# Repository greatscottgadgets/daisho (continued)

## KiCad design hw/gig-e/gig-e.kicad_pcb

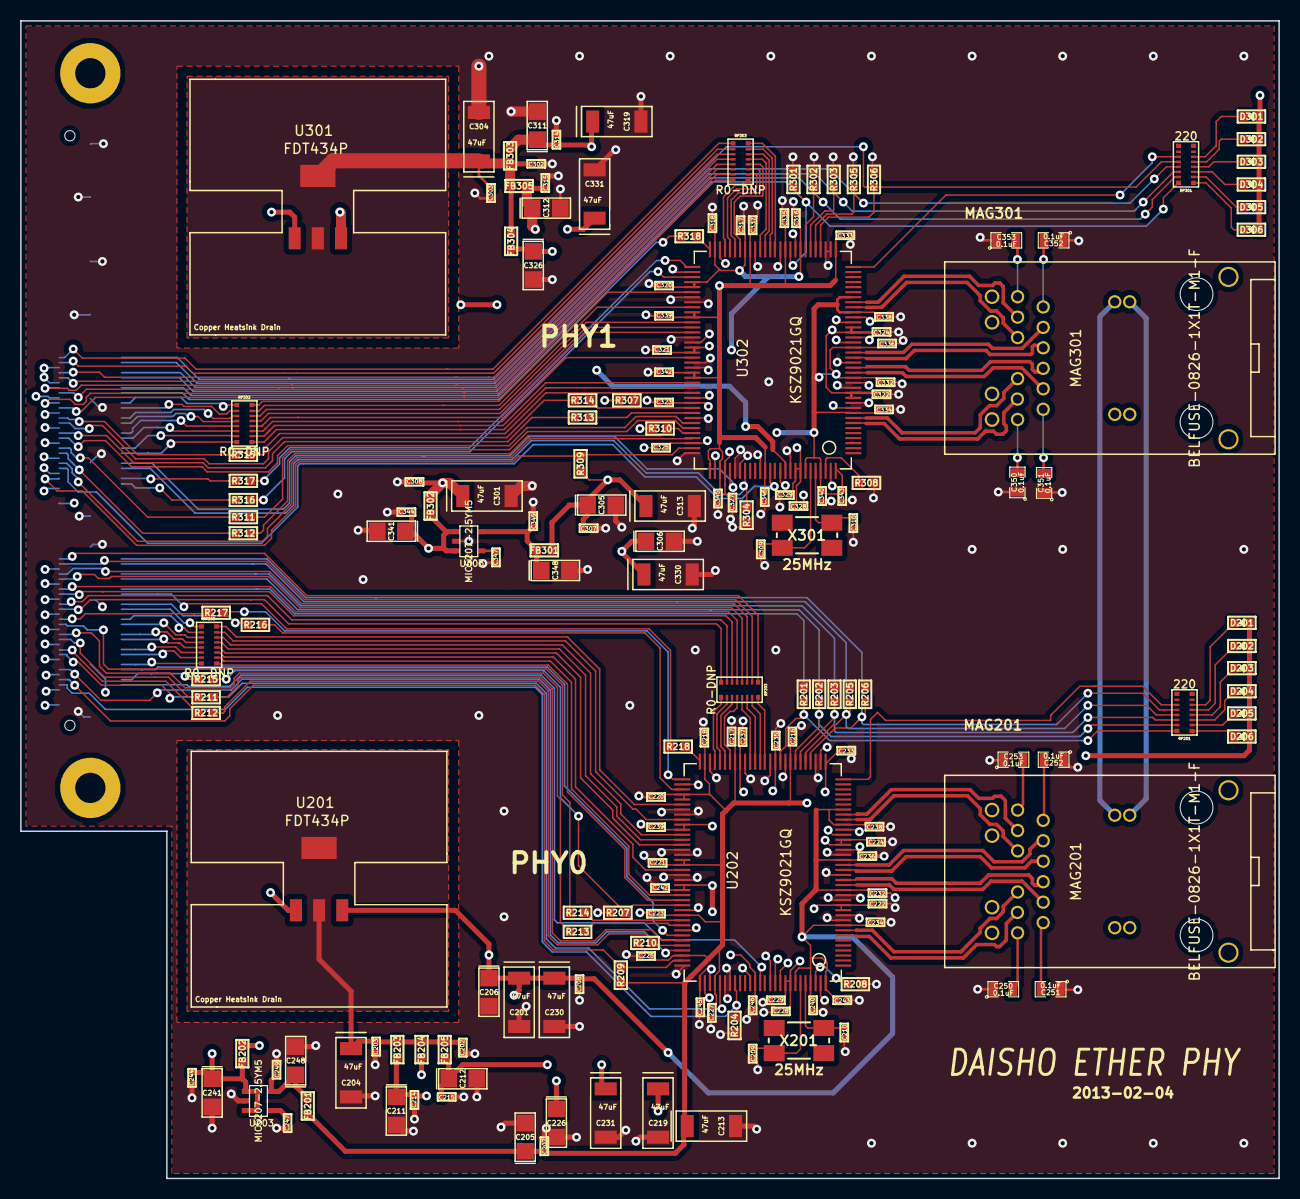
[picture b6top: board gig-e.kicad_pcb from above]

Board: 4 copper layers, 125.0 x 115.0 mm, 181 parts (1 on the bottom side), 185 nets.

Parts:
C201, C204, C213, C219, C230, C231, C301, C304, C313, C319, C330, C331: 47uF; gsg-2312
C202, C207, C208, C214, C215, C228, C244, C249, C302, C307, C308, C314, C315, C328, C344, C349: 0.1uF; GSG-0402
C203, C216, C217, C218, C220, C221, C222, C223, C224, C225, C227, C229, C232, C233, C234, C235, C236, C237, C238, C239, C240, C242, C243, C245, C246, C303, C316, C317, C318, C320, C321, C322, C323, C324, C325, C327, C329, C332, C333, C334, C335, C336, C337, C338, C339, C340, C342, C343, C345, C346: 10nF; GSG-0402
C205, C206, C211, C212, C226, C241, C248, C305, C306, C311, C312, C326, C341, C348: 10uF; gsg-sm1206p
C209, C210, C309, C310: 22pF; GSG-0402
C247, C347: 470pF; GSG-0402
C250, C251, C252, C253, C350, C351, C352, C353: 0.1uF; SM0805
D201: PHY0_LINK10-YLW; GSG-0603D
D202: PHY0_LINK100-GRN; GSG-0603D
D203: PHY0_LINK1000-BLUE; GSG-0603D
D204: PHY0_DUPLEX-YLW; GSG-0603D
D205: PHY0_RX-GRN; GSG-0603D
D206: PHY0_TX-GRN; GSG-0603D
D301: PHY1_LINK10-YLW; GSG-0603D
D302: PHY1_LINK100-GRN; GSG-0603D
D303: PHY1_LINK1000-BLUE; GSG-0603D
D304: PHY1_DUPLEX-YLW; GSG-0603D
D305: PHY1_RX-GRN; GSG-0603D
D306: PHY1_TX-GRN; GSG-0603D
FB201, FB202, FB203, FB204, FB205, FB301, FB302, FB303, FB304, FB305: FBEAD; GSG-0603
JP101: TERASIC-HSMC; TERASIC-HSMC-WITH-MOUNTS
MAG201, MAG301: BELFUSE-0826-1X1T-M1-F; BELFUSE-MAG
R201, R202, R203, R205, R206, R207, R301, R302, R303, R305, R306, R307: 1k; GSG-0603
R204, R304: 4.7k; GSG-0603
R208, R308: 4.99K 1%; GSG-0603
R209, R210, R309, R310: 4.7K; GSG-0603
R211, R212, R213, R214, R215, R216, R217, R218, R311, R312, R313, R314, R315, R316, R317, R318: 0.0-NP; GSG-0603
RP201, RP301: 220; 1506-RPACK
RP202, RP203, RP302, RP303: R0-DNP; 1506-RPACK
U201, U301: FDT434P; FDT434P-SOT223
U202, U302: KSZ9021GQ; GSG-PQFP128
U203, U303: MIC5207-2.5YM5; SOT23-5
X201, X301: 25MHz; ABMM2

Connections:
+2.5V: C248.1, C249.1, C348.1, C349.1, FB201.1, FB301.1, U203.5, U303.5
+3.3V: C241.1, C244.1, C341.1, C344.1, FB202.1, FB302.1, JP101.45, JP101.51, JP101.57, JP101.63, JP101.69, JP101.75, JP101.81, JP101.87, JP101.93, JP101.99, JP101.105, JP101.111, JP101.117, JP101.123, JP101.129, JP101.135, JP101.141, JP101.147, JP101.153, JP101.159, U203.1, U203.3, U303.1, U303.3
/GigE Phy0/AVDDH: C201.1, C206.1, C208.1, C230.1, C232.1, C234.1, C236.1, C238.1, C240.1, C243.1, FB202.2, U201.S, U202.9, U202.16, U202.22, U202.29, U202.32, U202.122, U202.125, U202.128
/GigE Phy0/AVDDL: C211.1, C214.1, C219.1, C222.1, C224.1, FB203.2, U202.12, U202.13, U202.25, U202.26
/GigE Phy0/AVDDL_PMOS: C202.1, C203.1, C204.1, FB203.1, FB204.1, FB205.1, U201.D
/GigE Phy0/AVDD_PLL: C226.1, C228.1, C229.1, FB204.2, U202.120, U202.121
/GigE Phy0/DVDDH: C205.1, C207.1, C213.1, C216.1, C217.1, C218.1, C220.1, C221.1, C223.1, C225.1, C227.1, D201.1, D202.1, D203.1, D204.1, D205.1, D206.1, FB201.2, R209.1, R210.1, U202.46, U202.57, U202.63, U202.68, U202.69, U202.81, U202.82, U202.92, U202.100, U202.106
/GigE Phy0/DVDDL: C212.1, C215.1, C231.1, C233.1, C235.1, C237.1, C239.1, C242.1, C245.1, C246.1, FB205.2, U202.39, U202.49, U202.56, U202.74, U202.75, U202.86, U202.87, U202.103, U202.105, U202.114
/GigE Phy0/GTX_CLK: R217.1, U202.65
/GigE Phy0/LDO_O: U201.G, U202.118
/GigE Phy0/LED1_D: D206.2, RP201.9
/GigE Phy0/LED2_D: D205.2, RP201.10
/GigE Phy0/LED3_D: D204.2, RP201.11
/GigE Phy0/LED4_D: D203.2, RP201.12
/GigE Phy0/LED5_D: D202.2, RP201.13
/GigE Phy0/LED6: RP201.3, U202.38
/GigE Phy0/LED6_D: D201.2, RP201.14
/GigE Phy0/RXD0: RP202.1, U202.89
/GigE Phy0/RXD1: RP202.2, U202.88
/GigE Phy0/RXD2: RP202.3, U202.83
/GigE Phy0/RXD3: RP202.4, U202.78
/GigE Phy0/RXD4: RP202.5, U202.77
/GigE Phy0/RXD5: RP202.6, U202.76
/GigE Phy0/RXD6: RP202.7, U202.73
/GigE Phy0/RXD7: RP202.8, U202.70
/GigE Phy0/TXD0: RP203.8, U202.51
/GigE Phy0/TXD1: RP203.7, U202.52
/GigE Phy0/TXD2: RP203.6, U202.53
/GigE Phy0/TXD3: RP203.5, U202.54
/GigE Phy0/TXD4: RP203.4, U202.58
/GigE Phy0/TXD5: RP203.3, U202.59
/GigE Phy0/TXD6: RP203.2, U202.60
/GigE Phy0/TXD7: RP203.1, U202.61
/GigE Phy1/AVDDH: C301.1, C306.1, C308.1, C330.1, C332.1, C334.1, C336.1, C338.1, C340.1, C343.1, FB302.2, U301.S, U302.9, U302.16, U302.22, U302.29, U302.32, U302.122, U302.125, U302.128
/GigE Phy1/AVDDL: C311.1, C314.1, C319.1, C322.1, C324.1, FB303.2, U302.12, U302.13, U302.25, U302.26
/GigE Phy1/AVDD_PLL: C326.1, C328.1, C329.1, FB304.2, U302.120, U302.121
/GigE Phy1/DVDDH: C305.1, C307.1, C313.1, C316.1, C317.1, C318.1, C320.1, C321.1, C323.1, C325.1, C327.1, D301.1, D302.1, D303.1, D304.1, D305.1, D306.1, FB301.2, R309.1, R310.1, U302.46, U302.57, U302.63, U302.68, U302.69, U302.81, U302.82, U302.92, U302.100, U302.106
/GigE Phy1/DVDDL: C312.1, C315.1, C331.1, C333.1, C335.1, C337.1, C339.1, C342.1, C345.1, C346.1, FB305.2, U302.39, U302.49, U302.56, U302.74, U302.75, U302.86, U302.87, U302.103, U302.105, U302.114
/GigE Phy1/GTX_CLK: R317.1, U302.65
/GigE Phy1/LDO_O: U301.G, U302.118
/GigE Phy1/LED1_D: D306.2, RP301.9
/GigE Phy1/LED2_D: D305.2, RP301.10
/GigE Phy1/LED3_D: D304.2, RP301.11
/GigE Phy1/LED4_D: D303.2, RP301.12
/GigE Phy1/LED5_D: D302.2, RP301.13
/GigE Phy1/LED6: RP301.3, U302.38
/GigE Phy1/LED6_D: D301.2, RP301.14
/GigE Phy1/PHY1_AVDDL_PMOS: C302.1, C303.1, C304.1, FB303.1, FB304.1, FB305.1, U301.D
/GigE Phy1/RXD0: RP302.1, U302.89
/GigE Phy1/RXD1: RP302.2, U302.88
/GigE Phy1/RXD2: RP302.3, U302.83
/GigE Phy1/RXD3: RP302.4, U302.78
/GigE Phy1/RXD4: RP302.5, U302.77
/GigE Phy1/RXD5: RP302.6, U302.76
/GigE Phy1/RXD6: RP302.7, U302.73
/GigE Phy1/RXD7: RP302.8, U302.70
/GigE Phy1/TXD0: RP303.8, U302.51
/GigE Phy1/TXD1: RP303.7, U302.52
/GigE Phy1/TXD2: RP303.6, U302.53
/GigE Phy1/TXD3: RP303.5, U302.54
/GigE Phy1/TXD4: RP303.4, U302.58
/GigE Phy1/TXD5: RP303.3, U302.59
/GigE Phy1/TXD6: RP303.2, U302.60
/GigE Phy1/TXD7: RP303.1, U302.61
GND: C201.2, C202.2, C203.2, C204.2, C205.2, C206.2, C207.2, C208.2, C209.1, C210.1, C211.2, C212.2, C213.2, C214.2, C215.2, C216.2, C217.2, C218.2, C219.2, C220.2, C221.2, C222.2, C223.2, C224.2, C225.2, C226.2, C227.2, C228.2, C229.2, C230.2, C231.2, C232.2, C233.2, C234.2, C235.2, C236.2, C237.2, C238.2, C239.2, C240.2, C241.2, C242.2, C243.2, C244.2, C245.2, C246.2, C247.2, C248.2, C249.2, C250.1, C251.1, C252.1, C253.1, C301.2, C302.2, C303.2, C304.2, C305.2, C306.2, C307.2, C308.2, C309.1, C310.1, C311.2, C312.2, C313.2, C314.2, C315.2, C316.2, C317.2, C318.2, C319.2, C320.2, C321.2, C322.2, C323.2, C324.2, C325.2, C326.2, C327.2, C328.2, C329.2, C330.2, C331.2, C332.2, C333.2, C334.2, C335.2, C336.2, C337.2, C338.2, C339.2, C340.2, C341.2, C342.2, C343.2, C344.2, C345.2, C346.2, C347.2, C348.2, C349.2, C350.1, C351.1, C352.1, C353.1, JP101.161, JP101.162, JP101.163, JP101.164, JP101.165, JP101.166, JP101.167, JP101.168, JP101.169, JP101.170, JP101.171, JP101.172, R201.2, R202.2, R203.2, R204.2, R205.2, R206.2, R207.2, R208.1, R301.2, R302.2, R303.2, R304.2, R305.2, R306.2, R307.2, R308.1, U202.10, U202.11, U202.14, U202.15, U202.19, U202.23, U202.24, U202.27, U202.28, U202.40, U202.41, U202.47, U202.50, U202.55, U202.62, U202.66, U202.71, U202.72, U202.79, U202.80, U202.84, U202.85, U202.91, U202.95, U202.102, U202.104, U202.108, U202.109, U202.113, U202.117, U202.119, U202.127, U203.2, U302.10, U302.11, U302.14, U302.15, U302.19, U302.23, U302.24, U302.27, U302.28, U302.40, U302.41, U302.47, U302.50, U302.55, U302.62, U302.66, U302.71, U302.72, U302.79, U302.80, U302.84, U302.85, U302.91, U302.95, U302.102, U302.104, U302.108, U302.109, U302.113, U302.117, U302.119, U302.127, U303.2
MAG_VC_1: MAG201.13, MAG301.13
MAG_VC_2: MAG201.14, MAG301.14
MAG_VC_3: MAG201.15, MAG301.15
MAG_VC_4: MAG201.16, MAG301.16
unnamed: R208.2, U202.126
unnamed: C253.2, MAG201.7
unnamed: C251.2, MAG201.6
unnamed: C252.2, MAG201.1
unnamed: C250.2, MAG201.12
unnamed: C247.1, U203.4
unnamed: C209.2, U202.123, X201.2
unnamed: C210.2, U202.124, X201.1
unnamed: R308.2, U302.126
unnamed: C353.2, MAG301.7
unnamed: C351.2, MAG301.6
unnamed: C352.2, MAG301.1
unnamed: C350.2, MAG301.12
unnamed: C347.1, U303.4
unnamed: C309.2, U302.123, X301.2
unnamed: C310.2, U302.124, X301.1
PHY0_CLK125_NDO: JP101.139, U202.107
PHY0_COL: JP101.145, U202.99
PHY0_CRS: JP101.146, U202.96
PHY0_GM_GTK_CLK: JP101.125, R217.2
PHY0_GM_MDC: JP101.133, R211.2
PHY0_GM_MIO: JP101.137, R212.2
PHY0_GM_RXD0: JP101.144, RP202.16
PHY0_GM_RXD1: JP101.140, RP202.15
PHY0_GM_RXD2: JP101.138, RP202.14
PHY0_GM_RXD3: JP101.134, RP202.13
PHY0_GM_RXD4: JP101.132, RP202.12
PHY0_GM_RXD5: JP101.128, RP202.11
PHY0_GM_RXD6: JP101.126, RP202.10
PHY0_GM_RXD7: JP101.122, RP202.9
PHY0_GM_RXDV: JP101.150, R215.2
PHY0_GM_RX_CLK: JP101.131, R213.2
PHY0_GM_RX_ERR: JP101.127, R214.2
PHY0_GM_TXD0: JP101.101, RP203.9
PHY0_GM_TXD1: JP101.103, RP203.10
PHY0_GM_TXD2: JP101.107, RP203.11
PHY0_GM_TXD3: JP101.109, RP203.12
PHY0_GM_TXD4: JP101.113, RP203.13
PHY0_GM_TXD5: JP101.115, RP203.14
PHY0_GM_TXD6: JP101.119, RP203.15
PHY0_GM_TXD7: JP101.121, RP203.16
PHY0_GM_TX_EN: JP101.120, R216.2
PHY0_GM_TX_ER: JP101.116, R218.2
PHY0_HW_RST: JP101.151, R204.1, U202.110
PHY0_INT_N: JP101.149, R209.2, U202.101
PHY0_MDC: R211.1, U202.97
PHY0_MDIO: R210.2, R212.1, U202.98
PHY0_PHYADDR0: JP101.114, R201.1, RP201.8, U202.48
PHY0_PHYADDR1: JP101.110, R202.1, RP201.7, U202.45
PHY0_PHYADDR2: JP101.108, R203.1, RP201.6, U202.44
PHY0_PHYADDR3: JP101.104, R205.1, RP201.5, U202.43
PHY0_PHYADDR4: JP101.102, R206.1, RP201.4, U202.42
PHY0_RXDV: R207.1, R215.1, U202.90
PHY0_RX_CLK: R213.1, U202.94
PHY0_RX_ERR: R214.1, U202.93
PHY0_TXRXM_A: MAG201.10, U202.8
PHY0_TXRXM_B: MAG201.4, U202.18
PHY0_TXRXM_C: MAG201.2, U202.21
PHY0_TXRXM_D: MAG201.8, U202.31
PHY0_TXRXP_A: MAG201.11, U202.7
PHY0_TXRXP_B: MAG201.5, U202.17
PHY0_TXRXP_C: MAG201.3, U202.20
PHY0_TXRXP_D: MAG201.9, U202.30
PHY0_TX_CLK: JP101.152, U202.115
PHY0_TX_EN: R216.1, U202.67
PHY0_TX_ER: R218.1, U202.64
PHY1_CLK125_NDO: JP101.84, U302.107
PHY1_COL: JP101.83, U302.99
PHY1_CRS: JP101.73, U302.96
PHY1_GM_GTK_CLK: JP101.90, R317.2
PHY1_GM_MDC: JP101.77, R311.2
PHY1_GM_MIO: JP101.79, R312.2
PHY1_GM_RXD0: JP101.80, RP302.16
PHY1_GM_RXD1: JP101.78, RP302.15
PHY1_GM_RXD2: JP101.74, RP302.14
PHY1_GM_RXD3: JP101.72, RP302.13
PHY1_GM_RXD4: JP101.68, RP302.12
PHY1_GM_RXD5: JP101.66, RP302.11
PHY1_GM_RXD6: JP101.62, RP302.10
PHY1_GM_RXD7: JP101.60, RP302.9
PHY1_GM_RXDV: JP101.65, R315.2
PHY1_GM_RX_CLK: JP101.71, R313.2
PHY1_GM_RX_ERR: JP101.67, R314.2
PHY1_GM_TXD0: JP101.41, RP303.9
PHY1_GM_TXD1: JP101.43, RP303.10
PHY1_GM_TXD2: JP101.47, RP303.11
PHY1_GM_TXD3: JP101.49, RP303.12
PHY1_GM_TXD4: JP101.53, RP303.13
PHY1_GM_TXD5: JP101.55, RP303.14
PHY1_GM_TXD6: JP101.59, RP303.15
PHY1_GM_TXD7: JP101.61, RP303.16
PHY1_GM_TX_EN: JP101.92, R316.2
PHY1_GM_TX_ER: JP101.56, R318.2
PHY1_HW_RST: JP101.86, R304.1, U302.110
PHY1_INT_N: JP101.89, R309.2, U302.101
PHY1_MDC: R311.1, U302.97
PHY1_MDIO: R310.2, R312.1, U302.98
PHY1_PHYADDR0: JP101.54, R301.1, RP301.8, U302.48
PHY1_PHYADDR1: JP101.50, R302.1, RP301.7, U302.45
PHY1_PHYADDR2: JP101.48, R303.1, RP301.6, U302.44
PHY1_PHYADDR3: JP101.44, R305.1, RP301.5, U302.43
PHY1_PHYADDR4: JP101.42, R306.1, RP301.4, U302.42
PHY1_RXDV: R307.1, R315.1, U302.90
PHY1_RX_CLK: R313.1, U302.94
PHY1_RX_ERR: R314.1, U302.93
PHY1_TXRXM_A: MAG301.10, U302.8
PHY1_TXRXM_B: MAG301.4, U302.18
PHY1_TXRXM_C: MAG301.2, U302.21
PHY1_TXRXM_D: MAG301.8, U302.31
PHY1_TXRXP_A: MAG301.11, U302.7
PHY1_TXRXP_B: MAG301.5, U302.17
PHY1_TXRXP_C: MAG301.3, U302.20
PHY1_TXRXP_D: MAG301.9, U302.30
PHY1_TX_CLK: JP101.85, U302.115
PHY1_TX_EN: R316.1, U302.67
PHY1_TX_ER: R318.1, U302.64

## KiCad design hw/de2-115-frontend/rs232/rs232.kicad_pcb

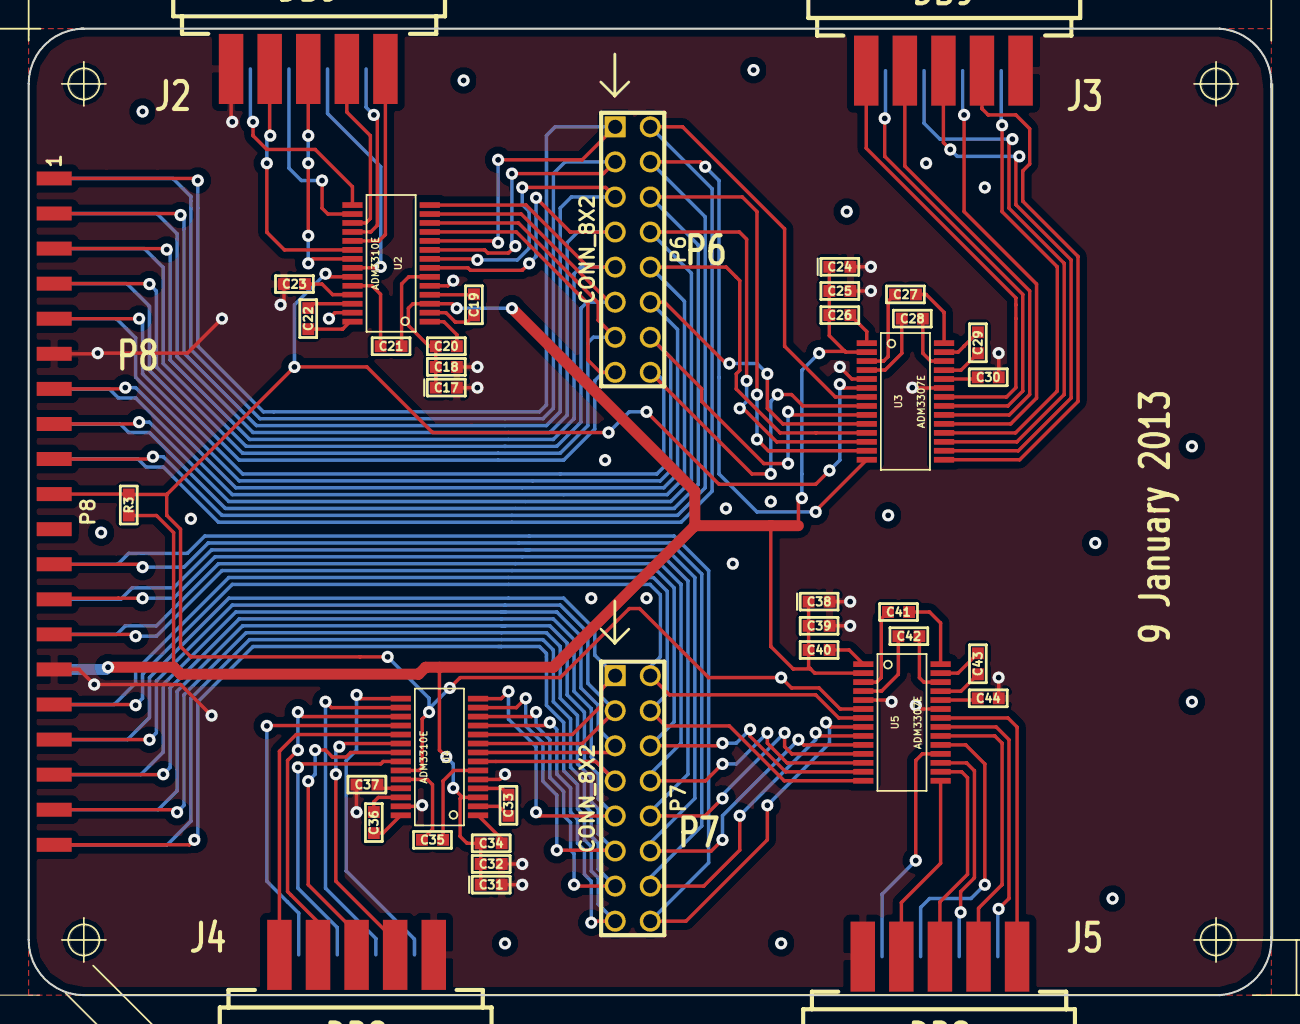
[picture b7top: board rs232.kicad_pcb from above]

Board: 2 copper layers, 90.0 x 70.0 mm, 41 parts (0 on the bottom side), 99 nets.

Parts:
70mm: 90mm; dp_devices-PCB7X9
C17, C24, C31, C38: T10uF; GSG-0603P
C18, C19, C20, C21, C22, C23, C25, C26, C27, C28, C29, C30, C32, C33, C34, C35, C36, C37, C39, C40, C41, C42, C43, C44: 0.1uF; GSG-0603
J2, J4: DB9; DB9M_CI
J3, J5: DB9; DB9F_CI
P6, P7: CONN_8X2; pin_array_8x2
P8: CONN_20X2; GSG-HEADER-2x20-EDGE
R3: 10K; GSG-0603
U2, U4: ADM3310E; tssop-28
U3, U5: ADM3307E; tssop-28

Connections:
+3.3V: C17.1, C18.1, C20.2, C24.1, C25.1, C26.1, C31.1, C32.1, C34.2, C38.1, C39.1, C40.1, P8.29, R3.2, U2.3, U3.2, U4.3, U5.2
/Pair A-B/CD-A-232: J2.1, U2.19
/Pair A-B/CD-B-232: J3.1, U3.22
/Pair A-B/CTS-A-232: J2.8, U2.16
/Pair A-B/CTS-B-232: J3.8, U3.19
/Pair A-B/DSR-A-232: J2.6, U2.18
/Pair A-B/DSR-B-232: J3.6, U3.21
/Pair A-B/DTR-A-232: J2.4, U2.20
/Pair A-B/DTR-B-232: J3.4, U3.15
/Pair A-B/RI-A-232: J2.9, U2.15
/Pair A-B/RI-B-232: J3.9, U3.18
/Pair A-B/RTS-A-232: J2.7, U2.22
/Pair A-B/RTS-B-232: J3.7, U3.17
/Pair A-B/RXD-A-232: J2.2, U2.17
/Pair A-B/RXD-B-232: J3.2, U3.20
/Pair A-B/TXD-A-232: J2.3, U2.21
/Pair A-B/TXD-B-232: J3.3, U3.16
/Pair C-D/CD-C-232: J4.1, U4.19
/Pair C-D/CD-D-232: J5.1, U5.22
/Pair C-D/CTS-C-232: J4.8, U4.16
/Pair C-D/CTS-D-232: J5.8, U5.19
/Pair C-D/DSR-C-232: J4.6, U4.18
/Pair C-D/DSR-D-232: J5.6, U5.21
/Pair C-D/DTR-C-232: J4.4, U4.20
/Pair C-D/DTR-D-232: J5.4, U5.15
/Pair C-D/RI-C-232: J4.9, U4.15
/Pair C-D/RI-D-232: J5.9, U5.18
/Pair C-D/RTS-C-232: J4.7, U4.22
/Pair C-D/RTS-D-232: J5.7, U5.17
/Pair C-D/RXD-C-232: J4.2, U4.17
/Pair C-D/RXD-D-232: J5.2, U5.20
/Pair C-D/TXD-C-232: J4.3, U4.21
/Pair C-D/TXD-D-232: J5.3, U5.16
CD-A-TTL: P6.1, P8.2, U2.10
CD-B-TTL: P6.2, P8.17, U3.7
CD-C-TTL: P7.1, P8.33, U4.10
CD-D-TTL: P7.2, P8.32, U5.7
CTS-A-TTL: P6.11, P8.5, U2.13
CTS-B-TTL: P6.12, P8.14, U3.10
CTS-C-TTL: P7.11, P8.38, U4.13
CTS-D-TTL: P7.12, P8.25, U5.10
DSR-A-TTL: P6.15, P8.7, U2.11
DSR-B-TTL: P6.16, P8.10, U3.8
DSR-C-TTL: P7.15, P8.40, U4.11
DSR-D-TTL: P7.16, P8.23, U5.8
DTR-A-TTL: P6.3, P8.1, U2.9
DTR-B-TTL: P6.4, P8.18, U3.14
DTR-C-TTL: P7.3, P8.34, U4.9
DTR-D-TTL: P7.4, P8.31, U5.14
GND: C17.2, C18.2, C23.2, C24.2, C25.2, C30.1, C31.2, C32.2, C37.2, C38.2, C39.2, C44.1, J2.5, J3.5, J4.5, J5.5, P8.12, P8.30, U2.5, U2.27, U3.5, U3.23, U4.5, U4.27, U5.5, U5.23
unnamed: C22.1, U2.26
unnamed: C30.2, U3.24
unnamed: C29.1, U3.27
unnamed: C22.2, U2.28
unnamed: C26.2, U3.1
unnamed: C28.1, U3.26
unnamed: C27.1, U3.28
unnamed: C29.2, U3.25
unnamed: C21.1, U2.6
unnamed: C21.2, U2.24
unnamed: C19.1, U2.2
unnamed: C20.1, U2.1
unnamed: C19.2, U2.4
unnamed: C23.1, U2.25
unnamed: C27.2, U3.3
unnamed: C28.2, U3.4
unnamed: C37.1, U4.25
unnamed: C35.1, U4.6
unnamed: C34.1, U4.1
unnamed: C33.2, U4.4
unnamed: C43.2, U5.25
unnamed: C43.1, U5.27
unnamed: C44.2, U5.24
unnamed: C35.2, U4.24
unnamed: C36.2, U4.28
unnamed: C33.1, U4.2
unnamed: C36.1, U4.26
unnamed: C40.2, U5.1
unnamed: C42.1, U5.26
unnamed: C41.2, U5.3
unnamed: C41.1, U5.28
unnamed: C42.2, U5.4
RI-A-TTL: P6.9, P8.6, U2.14
RI-B-TTL: P6.10, P8.13, U3.11
RI-C-TTL: P7.9, P8.37, U4.14
RI-D-TTL: P7.10, P8.26, U5.11
RTS-A-TTL: P6.7, P8.3, U2.7
RTS-B-TTL: P6.8, P8.16, U3.12
RTS-C-TTL: P7.7, P8.36, U4.7
RTS-D-TTL: P7.8, P8.27, U5.12
RXD-A-TTL: P6.13, P8.8, U2.12
RXD-B-TTL: P6.14, P8.9, U3.9
RXD-C-TTL: P7.13, P8.39, U4.12
RXD-D-TTL: P7.14, P8.24, U5.9
SD-ALL-TTL: P8.20, R3.1, U2.23, U3.6, U4.23, U5.6
TXD-A-TTL: P6.5, P8.4, U2.8
TXD-B-TTL: P6.6, P8.15, U3.13
TXD-C-TTL: P7.5, P8.35, U4.8
TXD-D-TTL: P7.6, P8.28, U5.13

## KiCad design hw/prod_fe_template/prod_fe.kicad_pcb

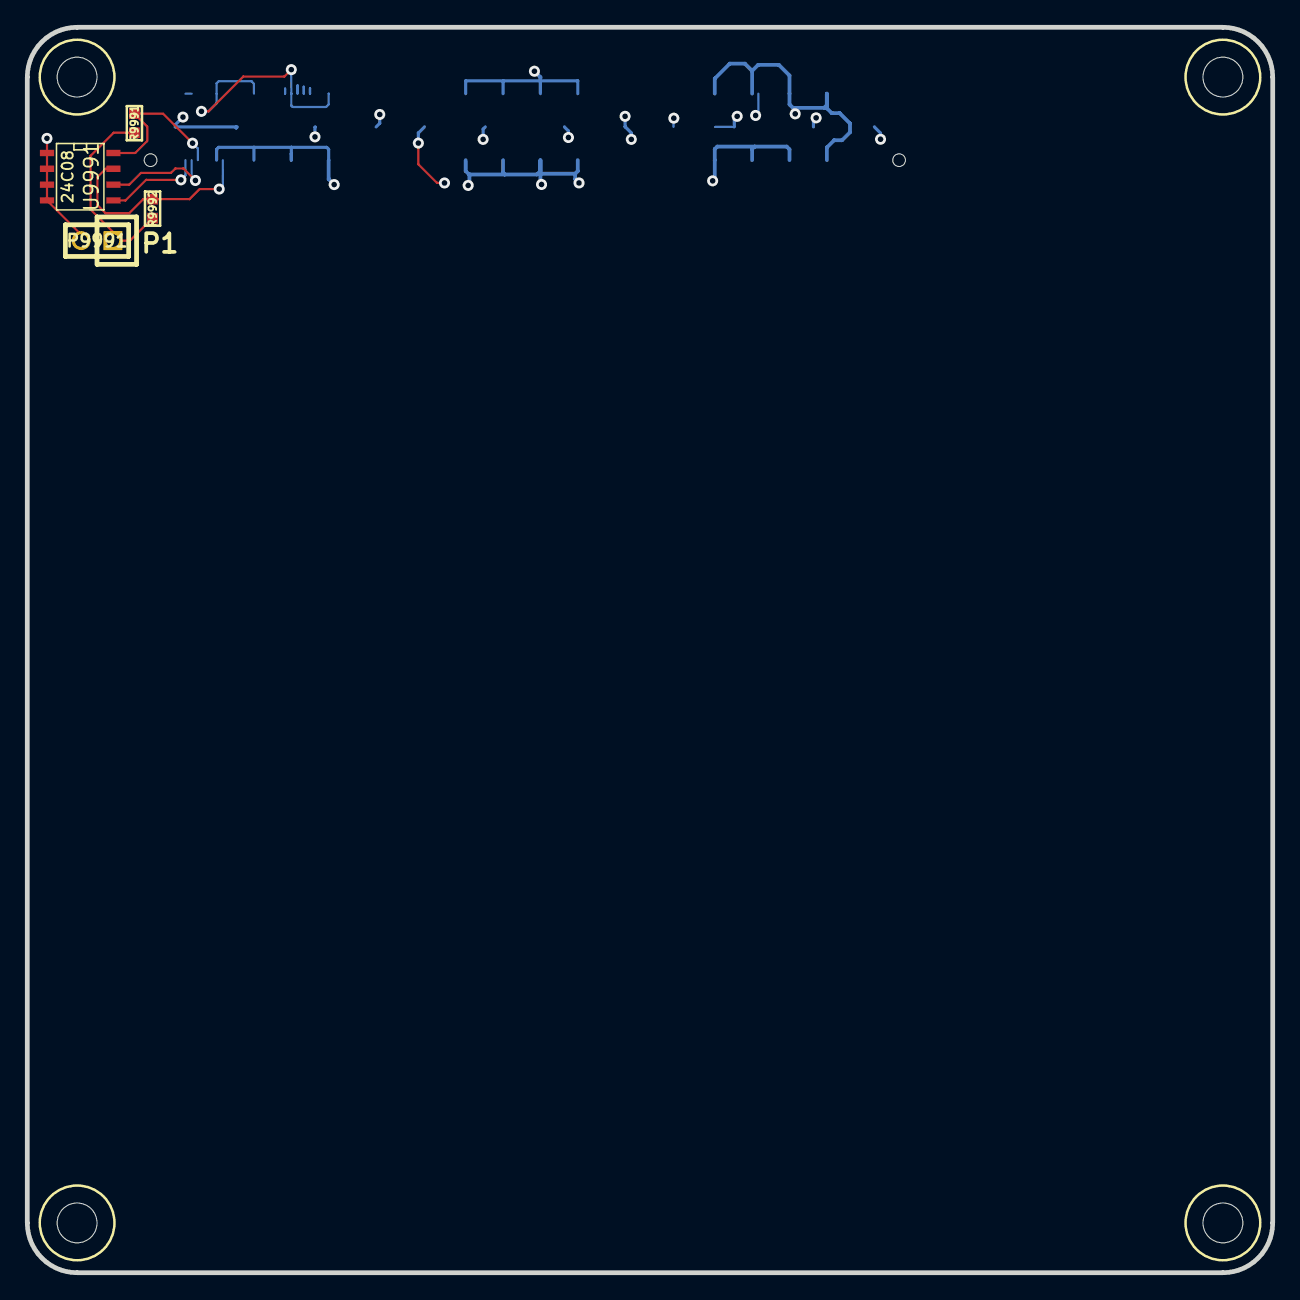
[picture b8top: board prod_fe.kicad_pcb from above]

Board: 4 copper layers, 100.0 x 100.0 mm, 9 parts (1 on the bottom side), 11 nets.

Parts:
H1, H2, H3, H4: HOLE; GSG-HOLE126MIL
J9991: SAMTEC_QSH-090-D; SAMTEC_QSH-090-01-F-D-A
P9991: CONN_2; GSG-HEADER-1x2
R9991, R9992: 10k; GSG-0603
U9991: 24C08; SO8E

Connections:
3V3A: J9991.12, J9991.24, J9991.36, J9991.48
3V3B: J9991.71, J9991.72, J9991.83, J9991.84, J9991.95, J9991.96, J9991.107, J9991.108
3V3C: J9991.131, J9991.132, J9991.143, J9991.144, J9991.155, J9991.156, J9991.167, J9991.168
/daisho_connector/FE_I2C_SCL: J9991.4, U9991.6
/daisho_connector/FE_I2C_SDA: J9991.2, U9991.5
/daisho_connector/VALT_FE: J9991.1, J9991.3
/daisho_connector/VRAW_SW: J9991.11, J9991.23, J9991.35, J9991.47
FE_I2C_EEPROM_WP: J9991.14, R9992.1, U9991.7
FE_I2C_VCC: J9991.6, R9991.1, U9991.8
GND: J9991.A0, J9991.A1, J9991.A2, J9991.A3, J9991.B0, J9991.B1, J9991.B2, J9991.B3, J9991.C0, J9991.C1, J9991.C2, J9991.C3, P9991.2, U9991.1, U9991.2, U9991.3, U9991.4
unnamed: P9991.1, R9991.2, R9992.2

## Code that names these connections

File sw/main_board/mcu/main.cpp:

/* 
 * Monulator ARM LPC11U14 application.
 * 
 * Copyright (C) 2013 Jared Boone, ShareBrained Technology, Inc.
 * 
 * This file is part of the Monulator project.
 * 
 * This program is free software; you can redistribute it and/or
 * modify it under the terms of the GNU General Public License
 * as published by the Free Software Foundation; either version 2
 * of the License, or (at your option) any later version.
 * 
 * This program is distributed in the hope that it will be useful,
 * but WITHOUT ANY WARRANTY; without even the implied warranty of
 * MERCHANTABILITY or FITNESS FOR A PARTICULAR PURPOSE.  See the
 * GNU General Public License for more details.
 * 
 * You should have received a copy of the GNU General Public License
 * along with this program; if not, write to the Free Software
 * Foundation, Inc., 51 Franklin Street, Fifth Floor, Boston, MA
 * 02110-1301, USA.
 */

#include "lpc11u.h"
#include "serial.h"

#include "i2c.h"
#include "si5351c.h"

#include <cstdint>

void turn_on_crystal_oscillator() {
	SCB.SYSOSCCTRL = 0;
	SCB.enable_power(SCB.PDRUNCFG_SYSOSC);
}

void start_system_pll() {
	// Start up system PLL: 12MHz crystal to 48 MHz.
	SCB.set_system_pll_dividers(1, 3);
	SCB.set_system_pll_clock_source(SCB.SYSPLLCLKSEL_SEL_CRYSTAL_OSCILLATOR);
	SCB.enable_power(SCB.PDRUNCFG_SYSPLL);
	SCB.wait_for_system_pll_lock();
}

void set_main_clock_to_system_pll() {
	// Switch main (and system clocks) to system PLL
	SCB.set_main_clock_source(SCB.MAINCLKSEL_SEL_PLL_OUTPUT);
}

void start_usb_pll() {
	// Start up USB PLL: 12MHz crystal to 48 MHz.
	SCB.set_usb_pll_dividers(1, 3);
	SCB.set_usb_pll_clock_source(SCB.USBPLLCLKSEL_SEL_SYSTEM_OSCILLATOR);
	SCB.enable_power(SCB.PDRUNCFG_USBPLL);
	SCB.wait_for_usb_pll_lock();
}

void set_usb_clock_to_main_clock() {
	// NOTE: Both clock sources must be running in order to switch!
	// So if you want to use the main clock instead of the USB PLL,
	// you have to start the USB PLL in order to switch away from it!
	SCB.set_usb_clock_source(SCB.USBCLKSEL_SEL_MAIN_CLOCK);
}

void set_usb_clock_to_usb_pll() {
	SCB.set_usb_clock_source(SCB.USBCLKSEL_SEL_USB_PLL_OUT);
}

void enable_peripheral_clocks() {
	SCB.set_system_clock_divider(1);
	SCB.enable_clocks(
		  SCB.SYSAHBCLKCTRL_GPIO
		//| SCB.SYSAHBCLKCTRL_CT16B0
		//| SCB.SYSAHBCLKCTRL_CT16B1
		//| SCB.SYSAHBCLKCTRL_CT32B0
		//| SCB.SYSAHBCLKCTRL_CT32B1
		| SCB.SYSAHBCLKCTRL_I2C
		| SCB.SYSAHBCLKCTRL_USART
		//| SCB.SYSAHBCLKCTRL_SSP1
		//| SCB.SYSAHBCLKCTRL_USB
		| SCB.SYSAHBCLKCTRL_IOCON
		//| SCB.SYSAHBCLKCTRL_RAM1	// Available on larger parts.
		| SCB.SYSAHBCLKCTRL_USBRAM
	);
}

void enable_clock_output() {
	SCB.set_clkout_clock_source(SCB.CLKOUTSEL_SEL_MAIN_CLOCK);
	SCB.set_clkout_divider(48);
	IOCON.PIO0_1 = 1;
}

void write_led_status(const uint_fast8_t value) {
	GPIO_PORT.write(0, 1, value);
}

void write_ddr2_sa(const uint_fast8_t value) {
	GPIO_PORT.write(0,  7, value & 2);
	GPIO_PORT.write(1, 24, value & 1);
}

void write_fe_en(const uint_fast8_t value) {
	GPIO_PORT.write(0, 20, value);
}

void fe_disable() {
	write_fe_en(0);
}

void fe_enable() {
	write_fe_en(1);
}

void write_v3p3a_enable(const uint_fast8_t value) {
	GPIO_PORT.write(0, 14, value);
}

void v3p3a_enable() {
	write_v3p3a_enable(1);
}

void v3p3a_disable() {
	write_v3p3a_enable(0);
}

void write_v2p5_enable(const uint_fast8_t value) {
	GPIO_PORT.write(0, 16, value);
}

void v2p5_enable() {
	write_v2p5_enable(1);
}

void v2p5_disable() {
	write_v2p5_enable(0);
}

void write_v1p8_enable(const uint_fast8_t value) {
	GPIO_PORT.write(1, 28, value);
}

void v1p8_enable() {
	write_v1p8_enable(1);
}

void v1p8_disable() {
	write_v1p8_enable(0);
}

void write_v1p2_enable(const uint_fast8_t value) {
	GPIO_PORT.write(0, 18, value);
}

void v1p2_enable() {
	write_v1p2_enable(1);
}

void v1p2_disable() {
	write_v1p2_enable(0);
}

void write_v1p1_enable(const uint_fast8_t value) {
	GPIO_PORT.write(0, 17, value);
}

void v1p1_enable() {
	write_v1p1_enable(1);
}

void v1p1_disable() {
	write_v1p1_enable(0);
}

void write_clockgen_oeb_n(const uint_fast8_t value) {
	GPIO_PORT.write(1, 14, value);
}

void clockgen_output_enable() {
	write_clockgen_oeb_n(0);
}

void clockgen_output_disable() {
	write_clockgen_oeb_n(1);
}

void write_v1px_smps_mode(const uint_fast8_t value) {
	GPIO_PORT.write(1, 25, value);
}

bool read_fpga_status() {
	return GPIO_PORT.read(1, 16) == 0;
}

bool read_fpga_conf_done() {
	return GPIO_PORT.read(0, 19) == 1;
}

void configure_pins() {
	// Configure port 0 pin directions
	GPIO_PORT.DIR0 |=
		  (1 << 20)	// FE_EN
		| (1 << 18)	// V1P2_ENABLE
		| (1 << 17)	// V1P1_ENABLE
		| (1 << 16)	// V2P5_ENABLE
		| (1 << 14)	// V3P3A_ENABLE
		| (1 << 13)	// USB_POWER_EN
		| (1 <<  7)	// DDR2_SA1
		| (1 <<  1)	// LED_STATUS
		;
	
	// Configure port 1 pin directions
	GPIO_PORT.DIR1 |=
		  (1 << 28)	// V1P8_ENABLE
		| (1 << 25)	// V1PX_SMPS_MODE
		| (1 << 24)	// DDR2_SA0
		| (1 << 14)	// CLOCKGEN_OEB#
		;
	
	// Set GPIO initial pin values
	write_led_status(0);
	write_ddr2_sa(0);
	fe_disable();
	v3p3a_disable();
	v2p5_disable();
	v1p8_disable();
	v1p2_disable();
	v1p1_disable();
	clockgen_output_disable();
	write_v1px_smps_mode(0);
	
	bool enable_fpga_jtag_interface = false;
	
	// Set pin multiplexers and behaviors
	IOCON.PIO0_1 = 0;		// PIO0_1: LED_STATUS (out), TODO: PWM control.
	IOCON.PIO0_2 = 1;		// SSEL0: SD_CS#
	IOCON.PIO0_3 = 1;		// USB_VBUS, TODO: needs pull-down?
	IOCON.PIO0_4 = 1;		// SCL: I2C_SCL
	IOCON.PIO0_5 = 1;		// SDA: I2C_SDA
	IOCON.PIO0_6 = 1;		// USB_CONNECT#
	IOCON.PIO0_7 = 0;		// PIO0_7: DDR2_SA1 (out)
	IOCON.PIO0_8 = 1;		// MISO0: SD_MISO
	IOCON.PIO0_9 = 1;		// MOSI0: SD_MOSI
	IOCON.TDI_PIO0_11 = 1;	// PIO0_11: ALT_SW_STAT (in)
	IOCON.TMS_PIO0_12 = 1;	// PIO0_12: USB_POWER_FLT# (in)
	IOCON.TDO_PIO0_13 = 1;	// PIO0_13: USB_POWER_EN (out)
	IOCON.TRST_PIO0_14 = 1;	// PIO0_14: V3P3A_ENABLE (out)
	IOCON.PIO0_16 = 0;		// PIO0_16: V2P5_ENABLE (out)
	IOCON.PIO0_17 = 0;		// PIO0_17: V1P1_ENABLE (out)
	IOCON.PIO0_18 = 0;		// PIO0_18: V1P2_ENABLE (out)
	IOCON.PIO0_19 = 0;		// PIO0_19: FPGA_CONF_DONE (in)
	IOCON.PIO0_20 = 0;		// PIO0_20: FE_EN (out)
	if( enable_fpga_jtag_interface ) {
		IOCON.PIO0_21 = 2;		// MOSI1: FPGA_TDI, TODO: Overloaded with SPI_MOSI
	} else {
		IOCON.PIO0_21 = 0;
	}
	IOCON.PIO0_22 = 3;		// MISO1: FPGA_MISO_V3P3, TODO: Overloaded with FPGA_TDO_V3P3
	IOCON.PIO0_23 = 0;		// PIO0_23: SD_DET (in)
	
	IOCON.PIO1_13 = 0;		// PIO1_13: CLOCKGEN_INTR# (in)
	IOCON.PIO1_14 = 0;		// PIO1_14: CLOCKGEN_OEB# (out)
	IOCON.PIO1_15 = 3;		// SCK1: SPI_SCK, TODO: Overloaded with FPGA_TCK
	IOCON.PIO1_16 = 0;		// PIO1_16: FPGA_NSTATUS (in)
	IOCON.PIO1_19 = 2;		// SSEL1: SPI_SS, TODO: Overloaded with FPGA_TMS
	if( enable_fpga_jtag_interface ) {
		IOCON.PIO1_20 = 2;		// SCK1: FPGA_TCK, TODO: Overloaded with SPI_SCK
		IOCON.PIO1_21 = 2;		// MISO1: FPGA_TDO_V3P3, TODO: Overloaded with FPGA_MISO_V3P3
	} else {
		IOCON.PIO1_20 = 0;
		IOCON.PIO1_21 = 0;
	}
	IOCON.PIO1_22 = 2;		// MOSI1: SPI_MOSI, TODO: Overloaded with FPGA_TDI
	if( enable_fpga_jtag_interface ) {
		IOCON.PIO1_23 = 2;		// SSEL1: FPGA_TMS, TODO: Overloaded with SPI_SS
	} else {
		IOCON.PIO1_23 = 0;
	}
	IOCON.PIO1_24 = 0;		// PIO1_24: DDR2_SA0 (out)
	IOCON.PIO1_25 = 0;		// PIO1_25: V1PX_SMPS_MODE (out)
	IOCON.PIO1_26 = 2;		// RXD: RXD
	IOCON.PIO1_27 = 2;		// TXD: TXD
	IOCON.PIO1_28 = 0;		// PIO1_28: V1P8_ENABLE (out)
	IOCON.PIO1_29 = 1;		// SCK0: SD_SCK
	IOCON.PIO1_31 = 0;		// PIO1_31: V1P8_PWRGD (in)
	
	SCB.enable_power(SCB.PDRUNCFG_USBPAD);
}

extern "C" int main() {
	turn_on_crystal_oscillator();
	start_system_pll();
	start_usb_pll();
	set_main_clock_to_system_pll();
	enable_peripheral_clocks();
	serial_init();

	configure_pins();
	delay(1000000);
	
	//enable_clock_output();
	
	NVIC.enable_interrupts();

	//serial_write_string("main():loop");
	//serial_write_line();
	
	// Power for FPGA
	v1p2_enable();	// FPGA VCCINT
	v2p5_enable();	// FPGA PLLs?
	v1p8_enable();	// FPGA VCCIOs, DDR2.
	v1p1_enable();	// USB internal voltage
	delay(1000000);

	// Power for the clock generator.
	// V3P3A must be turned on *after* V1P8 to satisfy
	// Si5351C requirement.
	v3p3a_enable();
	delay(1000000);
	
	// I2C configuration
	i2c0_init(500);
	
	// Give Si5351C time to power up?
	delay(100000);
	si5351c_disable_all_outputs();
	//si5351c_disable_oeb_pin_control();
	si5351c_power_down_all_clocks();
	si5351c_set_crystal_configuration();
	si5351c_enable_xo_and_ms_fanout();
	si5351c_configure_pll_sources_for_xtal();
	si5351c_configure_pll1_multisynth();
	
	si5351c_configure_multisynth(4, 1536, 0, 1, 0); // 50MHz
	si5351c_configure_multisynth(5, 1536, 0, 1, 0); // 50MHz
	si5351c_configure_multisynths_6_and_7();
	
	si5351c_configure_clock_control();
	si5351c_enable_clock_outputs();
	clockgen_output_enable();

	fe_enable();

	while(true) {
		//write_led_status(read_fpga_conf_done());
		write_led_status(1);
		delay(1000000);
		write_led_status(0);
		delay(1000000);
	}
	
	return 0;
}

extern "C" void SystemInit() {
	
}

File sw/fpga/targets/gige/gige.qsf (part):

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set_location_assignment PIN_G28 -to phy0_addr[2]
set_location_assignment PIN_C21 -to phy0_addr[1]
set_location_assignment PIN_D19 -to phy0_addr[0]
set_location_assignment PIN_G26 -to phy0_clk125_ndo
set_location_assignment PIN_F26 -to phy0_col
set_location_assignment PIN_D25 -to phy0_crs
set_location_assignment PIN_A17 -to phy0_gm_gtx_clk
set_location_assignment PIN_E26 -to phy0_mdc
set_location_assignment PIN_E25 -to phy0_mio
set_location_assignment PIN_J28 -to phy0_gm_rx_clk
set_location_assignment PIN_C25 -to phy0_gm_rx_dv
set_location_assignment PIN_A22 -to phy0_gm_rxd[7]
set_location_assignment PIN_B22 -to phy0_gm_rxd[6]
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set_location_assignment PIN_B25 -to phy0_gm_rxd[2]
set_location_assignment PIN_A26 -to phy0_gm_rxd[1]
set_location_assignment PIN_B26 -to phy0_gm_rxd[0]
set_location_assignment PIN_J27 -to phy0_tx_clk
set_location_assignment PIN_B17 -to phy0_gm_tx_en
set_location_assignment PIN_E18 -to phy0_gm_tx_er
set_location_assignment PIN_D18 -to phy0_gm_txd[7]
set_location_assignment PIN_C18 -to phy0_gm_txd[6]
set_location_assignment PIN_G21 -to phy0_gm_txd[5]
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set_location_assignment PIN_D15 -to phy0_gm_txd[2]
set_location_assignment PIN_C15 -to phy0_gm_txd[1]
set_location_assignment PIN_G20 -to phy0_gm_txd[0]
set_location_assignment PIN_F25 -to phy0_int_n
set_location_assignment PIN_F8 -to phy1_addr[2]
set_location_assignment PIN_B7 -to phy1_addr[1]
set_location_assignment PIN_A6 -to phy1_addr[0]
set_location_assignment PIN_C8 -to phy1_clk125_ndo
set_location_assignment PIN_E11 -to phy1_col
set_location_assignment PIN_E7 -to phy1_crs
set_location_assignment PIN_A8 -to phy1_gm_gtx_clk
set_location_assignment PIN_D14 -to phy1_mdc
set_location_assignment PIN_E14 -to phy1_mio
set_location_assignment PIN_A14 -to phy1_gm_rx_clk
set_location_assignment PIN_D13 -to phy1_gm_rx_dv
set_location_assignment PIN_A11 -to phy1_gm_rxd[7]
set_location_assignment PIN_B11 -to phy1_gm_rxd[6]
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set_location_assignment PIN_F7 -to phy1_gm_rxd[2]
set_location_assignment PIN_D8 -to phy1_gm_rxd[1]
set_location_assignment PIN_D10 -to phy1_gm_rxd[0]
set_location_assignment PIN_B14 -to phy1_tx_clk
set_location_assignment PIN_G8 -to phy1_gm_tx_en
set_location_assignment PIN_B6 -to phy1_gm_tx_er
set_location_assignment PIN_C7 -to phy1_gm_txd[7]
set_location_assignment PIN_D6 -to phy1_gm_txd[6]
set_location_assignment PIN_D5 -to phy1_gm_txd[5]
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set_location_assignment PIN_D4 -to phy1_gm_txd[2]
set_location_assignment PIN_C3 -to phy1_gm_txd[1]
set_location_assignment PIN_A3 -to phy1_gm_txd[0]
set_location_assignment PIN_E8 -to phy1_int_n
set_location_assignment PIN_B3 -to v1p2_en
set_location_assignment PIN_A4 -to v3p3_en
set_location_assignment PIN_G25 -to phy0_reset_n
set_location_assignment PIN_E12 -to phy1_reset_n
set_location_assignment PIN_E10 -to phy1_gm_rx_er
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
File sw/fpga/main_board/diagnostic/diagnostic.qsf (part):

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set_global_assignment -name PARTITION_NETLIST_TYPE SOURCE -section_id Top
set_global_assignment -name PARTITION_FITTER_PRESERVATION_LEVEL PLACEMENT_AND_ROUTING -section_id Top
set_global_assignment -name PARTITION_COLOR 16764057 -section_id Top
set_location_assignment PIN_R28 -to SPI_MOSI
set_location_assignment PIN_R26 -to SPI_SCK
set_location_assignment PIN_R25 -to SPI_SS
set_instance_assignment -name IO_STANDARD "1.8 V" -to SPI_MOSI
set_instance_assignment -name IO_STANDARD "1.8 V" -to SPI_SCK
set_instance_assignment -name IO_STANDARD "1.8 V" -to SPI_SS
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set_location_assignment PIN_AF5 -to I2C_SCL
set_location_assignment PIN_AG4 -to I2C_SDA
set_location_assignment PIN_R27 -to SPI_MISO
set_location_assignment PIN_Y28 -to CLK_N1
set_location_assignment PIN_Y27 -to CLK_P1
set_location_assignment PIN_AG14 -to CLK_P0
set_location_assignment PIN_AH14 -to CLK_N0
set_location_assignment PIN_AE16 -to DDR2_A[15]
set_location_assignment PIN_AC17 -to DDR2_A[14]
set_location_assignment PIN_AH10 -to DDR2_A[13]
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
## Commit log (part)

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2013-03-09 Reordering and rerouting high-speed signals to front-end connector. Got one more signal per bank along the outside (faster) layers. Still not quite what I want for USB 3.0, but probably acceptable.
2013-03-11 Reworked the front-end connector signals yet again. Trying to minimize trace lengths for as many traces as possible, increasing the length of other nets. Added a few top-level schematic placeholder p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
2013-03-11 Added and cleaned-up power network in schematic. Placed VCCIO regulators and components near front-end connector.
2013-03-11 Added a bunch of VCCIO bypass capacitors and tentatively placed them on the board.
2013-03-18 Added footprints for 0603 inductor, standard 5.0 x 3.2 mm crystal. Added symbol for grounding pads on 4-pin crystal/oscillator. Added USB power supply filtering, bypass caps. Moved TUSB1310A VSSOSC p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
2013-03-23 Add micro USB shield pin and name for EMI.
2013-03-23 Added IPC-standard SOT23 footprint.
2013-03-23 Fleshed out microcontroller on a new schematic sheet. Added (still empty) clock generator sheet.
2013-03-23 Fix up footprint library references for libraries renamed to IPC standard.
2013-03-23 NXP LPC11U1X LQFP48 footprint.
2013-03-24 Fleshed out clock generator schematic. Revised some power and clock distribution stuff. Renamed a couple of USB0 config signals to match TUSB1310A names.
2013-03-25 Extracted TPS62410 symbol from HackRF.
2013-04-02 Generic symbol and footprint for high-speed ESD protection IC. (Used for USB3.0)
2013-04-02 Review and clean-up of voltage supply architecture and clocking. Simplified top-level schematic by moving power nets into global labels. Moved and re-routed USB 3.0 interface IC (TUSB1310A) to bank 2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
2013-04-05 Almost successful routing of FPGA-to-DDR2 signals. Then I ran into SSN (signal switching noise?) issues, so I'll need to move some signals out of overused VREF groups. ARGHHHHH!
2013-04-07 Cleaning up DDR2 VREF topology. Cleaning up FPGA VREFs for front end banks.
2013-04-09 Fixed a few swapped differential pairs and mis-routed wires on front end bank C.
2013-04-10 Tweaks and initial layout of clock generation region.
2013-04-11 Milestone 33 - initial commit of buffer->endpoint No RS232 data tapped yet
2013-04-12 Completing power management sheet.
2013-04-12 Fixed surprise escaping in comment.
2013-04-12 MicroSD hooked up to microcontroller. Removed regulated supplies from front end connector, replaced with unregulated voltage.
2013-04-13 Extracted USB 2.0 protection IC from HackRF Jawbreaker.
2013-04-13 Symbol for TI TPS27081A Fancy Load Switch.
2013-04-13 Symbol for 74LVC2T45 two-channel voltage level shifter.
2013-04-13 Footprints for 74LVC2T45, MIC5207, TPS27081A. Fixed "clever" but ultimately misguided pinout on TPS27081A symbol.
2013-04-14 Generic 1206 (3216 metric) ceramic capacitor footprint.
2013-04-14 Footprint for larger 2A, 1.8V switcher inductor.
2013-04-14 Assorted component/value clean-up. Assorted footprint assignment. Values and tolerances for LDO regulator voltage resistors. Requirement attributes for switcher components. Manufacturer and part numb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
2013-04-15 More component/footprint mapping and fixing. Assigning BOM details to reference designators.
2013-04-15 Significant change in layout of power and microcontroller sections, trying to get everything on the board in a somewhat rational location. Still in progress, but starting to look good...
2013-04-16 Remove binary file from git
2013-04-17 More microcontroller control signal hook-up: DDR2 SPD, V1P8 regulator. Swapped I2C and VALT_FE pins on front end connector. Selected Schottky diodes, created package and specified in schematic/CvPCB.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
2013-04-19 Miscellaneous pin-swapping for signals to the microcontroller. Moved uC <-> FPGA SPI interface to FPGA bank 5. Relocated I2C pins on FPGA to route to DDR2 socket, to uncrowd the routing region betwee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
2013-04-21 Add pre-release comments to silkscreen and top/bottom copper and to PCB document, for quoting by PCB vendors. Add USB 3.0 ID pin support. Add project name/URL, release date, handwriting silkscreen bl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
2013-04-21 Don't use aux origin for Gerbers, drill file. Don't subtract mask from silk, let PCB vendor do that.
2013-04-22 Enlarged secondary V1P8 plane to cover region between TUSB1310A and FPGA. Knitted to other V1P8 plane with large vias. Shrunk V3P3 plane (unnecessarily large) to make room for above enlargement.
2013-04-22 Adjusted layer stack comment block to be more readable.
2013-04-24 Make state machine more readable
2013-04-25 Reordered layers to match Sunstone recommendation, improve impedance characteristics of internal signal layers. Updated layer stack info on PCB document to match Sunstone's recommendation.
2013-04-25 Adjusted solder mask clearance to 3mil, after deciding Sunstone's +/-5mil tolerance would result in an acceptable 2mil worst-case encroachment.
2013-04-26 Fixed up a few 50 Ohm traces with the wrong width.
2013-04-28 Exposed flag indicating that device has been configured. (And it's safe to start pumping bulk stuff.)
2013-04-30 Commit RS-232 pass-through test script
2013-05-01 Set pin assignments for GigE front-end board
2013-05-02 Remove unused pins to simplify project.
2013-05-02 Move redundant startup code in to separate module
2013-05-02 Improved pin 1 silkscreen markings on several small packages. Updated PCB with modified footprints.
2013-05-02 Regenerated netlist. Resaved component mapping file (.cmp). Changed mounting holes from plated to non-plated (since the drill and pad sizes were already equal). Added zone to improve grounding to HSM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
2013-05-07 Corrected design rules to match newer layer stack: minimum trace of 6.5mil, minimum clearance, 5.0mil. Altered 50 Ohm traces to new layer stack widths. Fixed up some non-50 Ohm traces that needed wid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
2013-05-08 Updated all modules (footprints). Re-read netlist. Reconnected traces to pads.
2013-05-22 Hacked up the Monulator code to provide a base for bringing up the main board. At present, the code will: - Switch to using an attached 12MHz crystal. - Initialize the serial port. - Initialize all G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
2013-06-05 Add I2C peripheral and I2C0 declarations.
2013-06-05 Add functions to read FPGA done/status signals.
2013-06-05 Add initialization code for I2C peripheral, Si5351C-B, and power supplies.
2013-06-05 Changed usb2_top interface to remove the data inout signal in favor of separate in/out/oe signals. This permits simpler control of signals at strapping (USB PHY reset) time. Updated RS232 target proj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
2013-06-18 Tidy GigE phy init code
2013-07-18 Allowed Quartus II to update LAST_QUARTUS_VERSION.
2013-07-22 Flip around bit order on phy<n>_addr signals.
2013-07-22 Add pins for UART on DE2-115.
2013-07-22 Rework reset switch capture.
2013-07-22 Rename reset_n to reset_i, use positive assertion.
2013-07-22 Pipe packet and nibble counts to DE2-115 LED displays, selectable by SW[0] and SW[1] positions.
2013-07-22 UART for transmitting RX or TX data to host for debugging.
2013-07-22 Fix small amount of commit-breakage from me trying to separate my commits.
2013-07-22 Fix indentation.
2013-07-28 Add a quick serial->pcap tool for Black Hat demo
2013-08-09 usb2/usb3: default FSM states, unbroken 2.0, prelim rx descrambling 3.0
2013-08-11 Black Hat demos
2013-08-16 usb3: preliminary TX scrambling
2013-09-16 usb3: continue link layer development
2013-10-09 usb3: link supporting additions
2013-10-24 Update rs232 top module to match changes to USB core.
2013-11-02 usb3: protocol layer, enumeration
2014-01-14 usb3: more error handling and milestone 29
2014-03-23 usb3: better power mgmt, compliance and milestone 30
2014-10-15 mainboard: removed gerbers
2014-10-15 Fixed pad positions on TE-1473005-4 DDR2 SO-DIMM socket.
2014-10-15 Add BARREL_JACK library, since it apparently existed only in my cache, or was otherwise disappeared from the KiCAD libraries. All the .sch files had to be updated because the list of LIBS appear in *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
2014-10-15 Fixed SS TX/RX swapped pairs on USB 3.0 connector. Moved USB 3.0 connector to "front" of board and cleaned up routing. Fixed DDR2 footprint and related routing. Reworked power routing near power conn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
2014-10-15 Add 50mil test point.
2014-10-15 FPGA JTAG is now a 2x5 0.1" header. Microcontroller UART now exposed on test points, not JTAG header. Moved general-purpose button to a better location and to a different pin on the microcontroller. 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
2014-10-15 Updated microcontroller USB connector. Moved silkscreen writing block. Ready (again) for review for next PCB build.
2014-10-15 SOIC footprints.
2014-10-15 Added footprint match to TUSB1310 library symbol.
2014-10-15 Remove USB PHY_RESETN pull-downs. Comments about PIPE and ULPI bus considerations, USB PHY pull-ups/downs strategy, USB diff pair and VBUS switch characteristics. Added bulk capacitance to input and 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
2014-10-15 Symbol: TPS54821 had un-numbered pin.
2014-10-15 TC6416A I/O expander symbol and footprint.
2014-10-15 USB: Initial README for PCB.
2014-10-15 Footprint: Bourns inductors SRN6045, SRR1260, SRR1280.
2014-10-15 PCB: Slight footprint pad adjustment.
2014-10-15 PCB: Allow .pro upgrade, incorporate Gerber export settings.
2014-10-15 KiCad: Quick and dirty PCB helper.
2014-10-15 PCB: Final clean-up
    HSMC grounding tweaks.
    Connect a ground island (still served by other ground plane, but...).
    Add clearance to some copper pours.
    Remove "DO NOT MANUFACTURE".
    Update PCB date code.
2014-10-15 Update USB schematic date.
2014-10-15 MCU: Enable front-end power at end of main board initialization.
2014-10-15 Rework RS-232 target project for new front-end board.
2014-10-15 moved front-end modules into subdirectories
2014-10-16 overhauled voltage regulators, added 3.3 V from VRAW
2014-10-17 new regulator enable signals
2014-10-19 overhauled clock generator section
2014-10-19 serdes updates
2014-10-22 settled on 2.5 V misc. I/O
2014-10-22 added missing FAN4860 lib
2014-10-26 corrected PHY pin 16: AVDDH, not AVDDL
2014-10-26 connect PHYAD2 through 10k resistors to allow strapping without interfering with clock function
2014-10-27 converted daisho.mod to .pretty
2014-10-27 PCB layer legend
2014-10-27 permanently pulled up V2P5_EN for FPGA I/O supply startup
2014-10-28 footprint assignments
2014-10-28 started layout by copying sections from previous HDMI board
2014-10-28 *.kicad_pcb-bak in .gitignore
2014-10-28 started mezzanine/serdes tracks
2014-10-28 more mezzanine tracks
2014-10-29 regulators
2014-10-29 round holes for HDMI connector
2014-10-30 little bom update
2014-10-30 changed C116 to 0603, pulled zones back from U11 pins for solderability
2014-10-30 ripped out obsolete STDVE001A, hoping TLK3134 equalizer is sufficient
2014-10-31 detect front-end module presence by VALT_FE for switching off mainboard IO bank supplies
2014-10-31 usb: added resistor for VALT_FE detection
2014-10-31 usb: layer legend
2014-10-31 rs232: added resistor for VALT_FE detection, EEPROM decoupling cap
2014-10-31 GigE: Initial 1000baseT passthrough and monitoring support
2014-11-01 rs232: updated to correct QSH footprint
2014-11-01 HDMI: Initial passthrough and monitoring.
2014-11-02 corrected SD_CH3_TXCLK name to SD_CH2_TXCLK
2014-11-03 clock generator layout
2014-11-03 hdmi: renamed layers
2014-11-03 hdmi: clock input notes
2014-11-03 hdmi: improved supply zones under BGA
2014-11-03 hdmi: connect HDMI shell to GND through ferrite instead of direct
2014-11-03 another forgotten module
2014-11-06 hdmi: LED silkscreen
2015-01-27 updated QFNs to module with corrected paste layer
2015-02-13 bom info
2015-02-13 made small headers DNP, made R63 not DNP, fixed J1 bom info
2015-02-27 fixed bom info
2015-03-11 daisho-eth: return -1 instead
    All other error cases, return -1, so fix this one
    case where it's returning 1 instead.
2015-03-11 daisho: also look at device 0
    If we do a pre-increment, we will never
    look at device 0, only 1 and all others.
    By doing a post-increment, we will also look
    at device 0.
2015-03-11 daisho-en-uart: miscellaneous cleanup
    indentation, white spaces, and the like.
2015-03-11 daisho-rs232: remove unnecessary dev check
    dev is always valid when that call happens.
2015-04-03 mainboard: reference tweaks for assembly diagram
2015-04-03 mainboard: DNP notes
